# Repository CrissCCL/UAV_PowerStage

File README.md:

# ⚡🔌🔋 UAV Power Distribution & Regulation Board

## Overview

This repository documents an **updated power stage for an unmanned aerial vehicle (UAV)**, developed as a **standalone PCB** to improve system modularity, robustness, and power integrity.

Originally, the power management circuitry was integrated on the same PCB as the **MCU, IMU, and control electronics**.  
In this revision, the power stage was **fully separated into a dedicated board**, enabling a clear functional separation between:

- **Power distribution and regulation**
- **Control, sensing, and navigation electronics**

This modular architecture simplifies debugging, testing, maintenance, and future system upgrades, while improving isolation between high-current and low-power domains.

## 📂 Contents
- `/Hardware` →  Schematic, Gerbers.

## 🌐 YouTube

📺 [Upgrade Power Stage](https://youtube.com/shorts/vSKApaUKDLE?feature=share)

## 🔗 Project Context

This power distribution and regulation board is part of the ongoing hardware updates for the **DIY UAV project**.

The main project repository documents the overall UAV system, including mechanical design, control architecture, and system integration:

- **DIY UAV – Main Project Repository**  
  [DIY UAV](https://github.com/CrissCCL/DIY_UAV)

This repository focuses exclusively on the **power stage modularization**, extracted from the original integrated PCB to improve system scalability, maintainability, and electrical robustness.

## 🧩 System Architecture

The UAV electronics are now divided into two main subsystems:

1. **Power Stage (this repository)**
2. **Control & Sensing Stage (MCU + IMU)**

The power board is responsible for managing the **battery input**, distributing high-current power to the ESCs, and providing regulated power for low-voltage electronics.

## 🔗 Power Flow Architecture

The power distribution follows a centralized architecture in which the battery input is first managed by a high-side power switch, and then distributed to both high-current and low-voltage domains.

## 🖼️ PCB Render Visualization

<table>
  <tr>
    <td align="center">
      <br>
      <sub> Power Stage PCB – Top View </sub>
    </td>
    <td align="center">
        <br>
      <sub>Power Stage PCB – Bottom View </sub>
    </td>
  </tr>
</table>

## ⚡ Physical Prototype

The following image shows the complete setup of the **prototype version**:

<table>
  <tr>
    <td align="center">
      <br>
      <sub> Power Stage PCB V1 – Top View </sub>
    </td>
    <td align="center">
        <br>
      <sub>Power Stage PCB V1 – Bottom View </sub>
    </td>
  </tr>
</table>

## 📸 In-System Integration (UAV Installation)

The following image shows the **power distribution board installed inside the UAV platform**, 
demonstrating real-world integration with the battery, ESCs, and avionics electronics.

<p align="center">
  <sub>Power Stage PCB installed inside the UAV frame – full system integration test</sub>
</p>

## ⚠️ Disclaimer

This project is intended **for educational and experimental purposes only**.

The power distribution and regulation board is **not flight-certified** and has not been validated under aviation or safety-critical standards.

Users are responsible for ensuring safe operation, proper electrical protection, and compliance with applicable regulations when working with high-current systems.

## 🤝 Support projects
 Support me on Patreon [https://www.patreon.com/c/CrissCCL](https://www.patreon.com/c/CrissCCL)

## 📜 License
MIT License

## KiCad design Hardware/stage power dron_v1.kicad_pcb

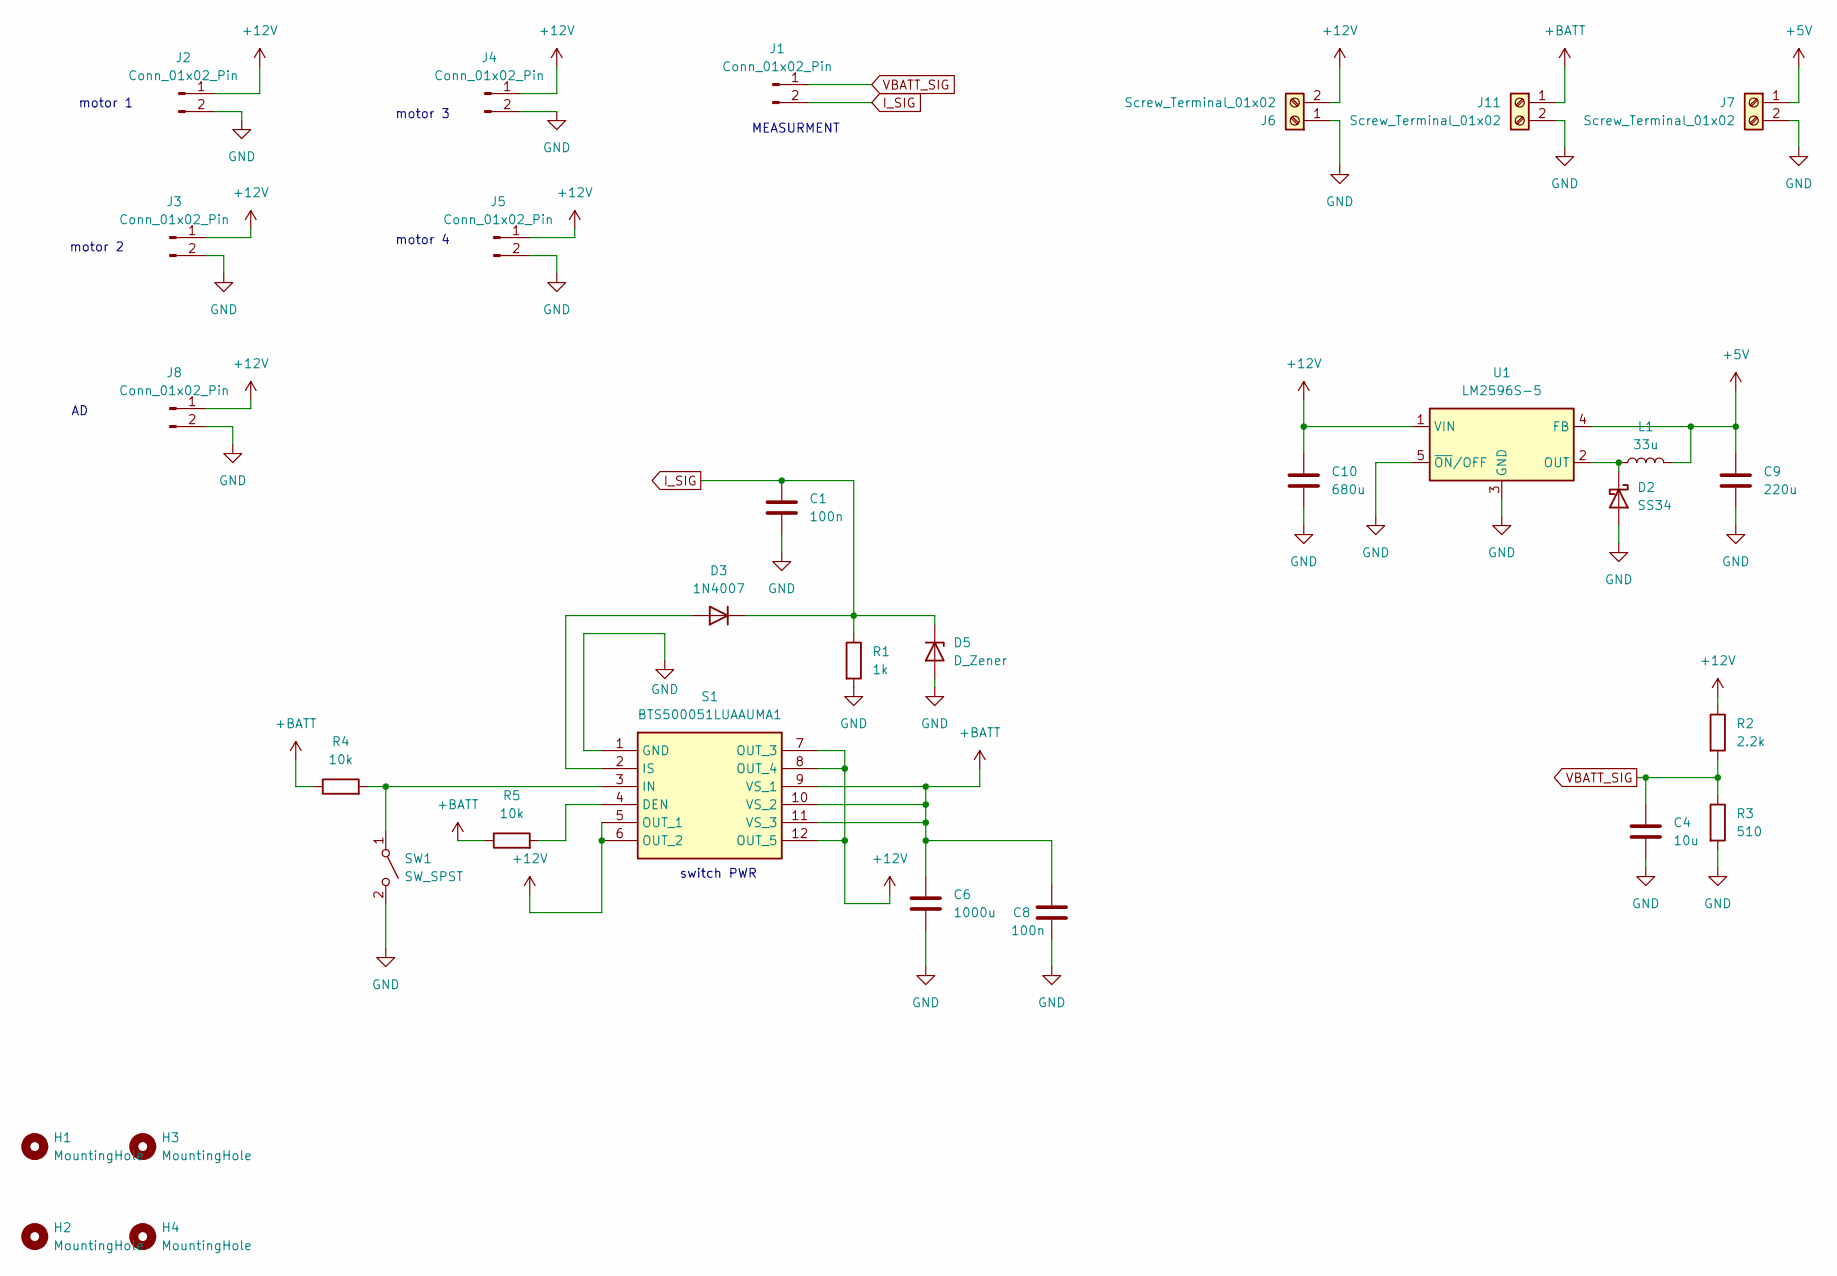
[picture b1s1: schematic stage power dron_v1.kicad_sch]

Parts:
C1, C8: 100n; C_1206_3216Metric_Pad1.33x1.80mm_HandSolder
C4: 10u; CP_Elec_4x5.4
C6: 1000u; CP_Elec_10x10.5
C9: 220u; CP_Elec_6.3x5.4
C10: 680u; CP_Elec_10x10.5
D2: SS34; D_SMA
D3: 1N4007; D_SOD-123
D5: D_Zener; D_MiniMELF
H1, H2, H3, H4: MountingHole; MountingHole_3.2mm_M3_ISO7380_Pad
J1: Conn_01x02_Pin; PinHeader_1x02_P2.54mm_Vertical
J2, J3, J4, J5, J8: Conn_01x02_Pin; conector_pad_1
J6, J7, J11: Screw_Terminal_01x02; TerminalBlock_bornier-2_P5.08mm
L1: 33u; L_12x12mm_H8mm
R1: 1k; R_1206_3216Metric_Pad1.30x1.75mm_HandSolder
R2: 2.2k; R_1206_3216Metric_Pad1.30x1.75mm_HandSolder
R3: 510; R_1206_3216Metric_Pad1.30x1.75mm_HandSolder
R4, R5: 10k; R_1206_3216Metric_Pad1.30x1.75mm_HandSolder
S1: BTS500051LUAAUMA1; Manufacturer_Part_Number BTS500051LUAAUMA1; Mouser Part Number 726-BTS500051LUAAUMA
SW1: SW_SPST; spst 1 grande
U1: LM2596S-5; TO-263-5_TabPin3

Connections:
+5V: C9.1, J7.1, L1.2, U1.4 (FB)
+12V: C10.1, J2.1, J3.1, J4.1, J5.1, J6.2, J8.1, R2.1, S1.5 (OUT_1), S1.6 (OUT_2), S1.7 (OUT_3), S1.8 (OUT_4), S1.12 (OUT_5), U1.1 (VIN)
+BATT: C6.1, C8.1, J11.1, R4.1, R5.1, S1.9 (VS_1), S1.10 (VS_2), S1.11 (VS_3)
GND: C1.2, C4.2, C6.2, C8.2, C9.2, C10.2, D2.2 (A), D5.2 (A), J2.2, J3.2, J4.2, J5.2, J6.1, J7.2, J8.2, J11.2, R1.2, R3.2, S1.1 (GND), SW1.2 (B), U1.3 (GND), U1.5 (~ON/OFF)
I_SIG: C1.1, D3.1 (K), D5.1 (K), J1.2, R1.1
unnamed: D2.1 (K), L1.1, U1.2 (OUT)
unnamed: D3.2 (A), S1.2 (IS)
unnamed: R5.2, S1.4 (DEN)
unnamed: R4.2, S1.3 (IN), SW1.1 (A)
VBATT_SIG: C4.1, J1.1, R2.2, R3.1

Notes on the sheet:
motor 4
motor 1
switch PWR
motor 2
motor 3
MEASURMENT

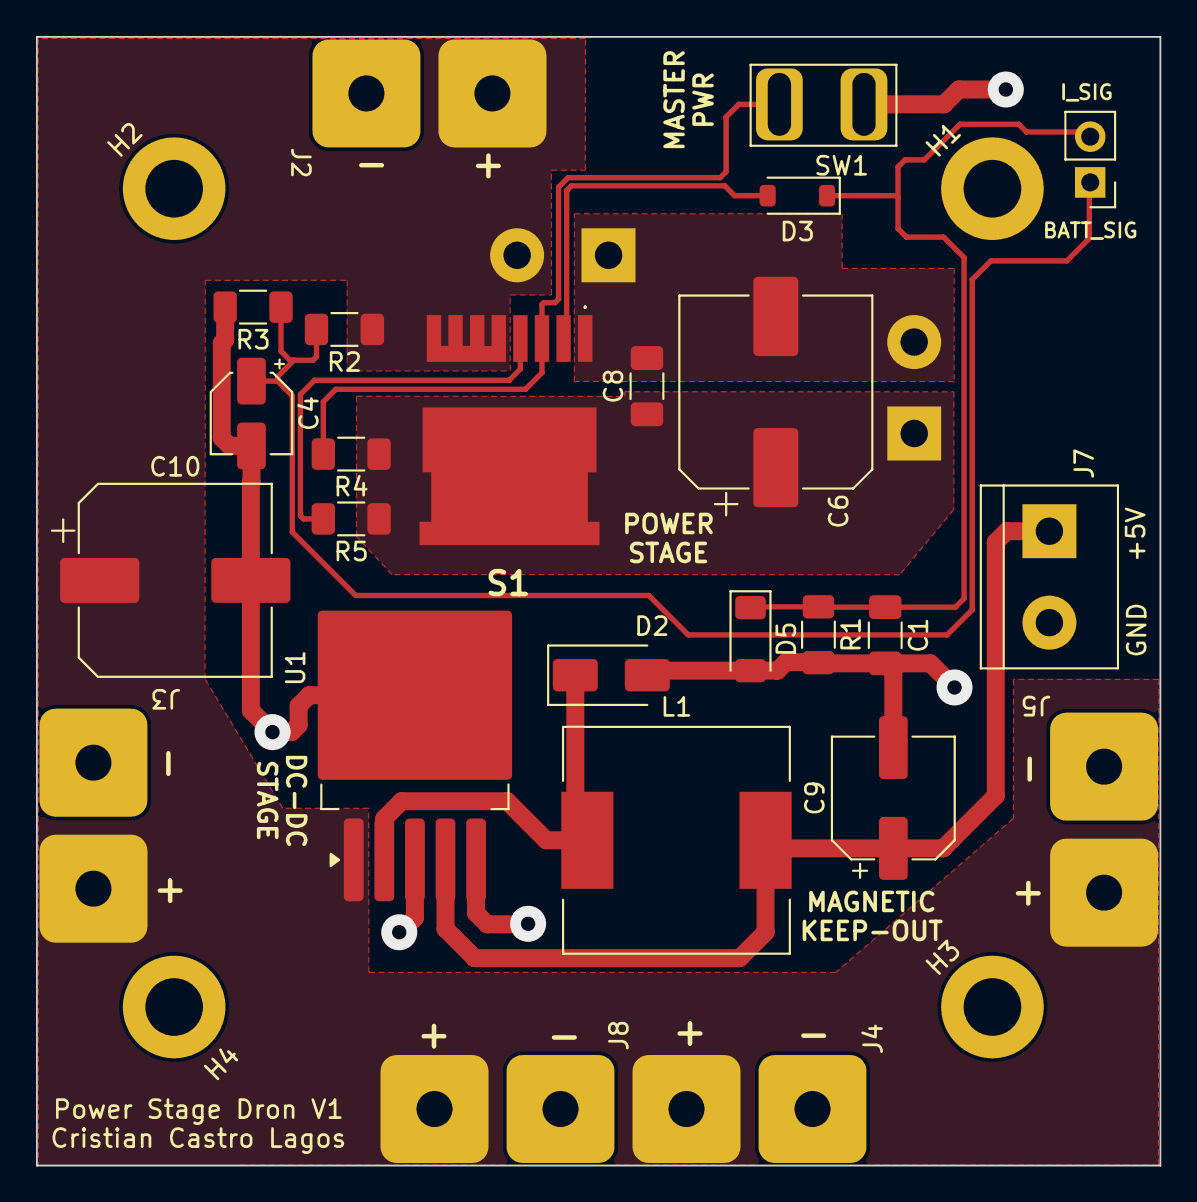
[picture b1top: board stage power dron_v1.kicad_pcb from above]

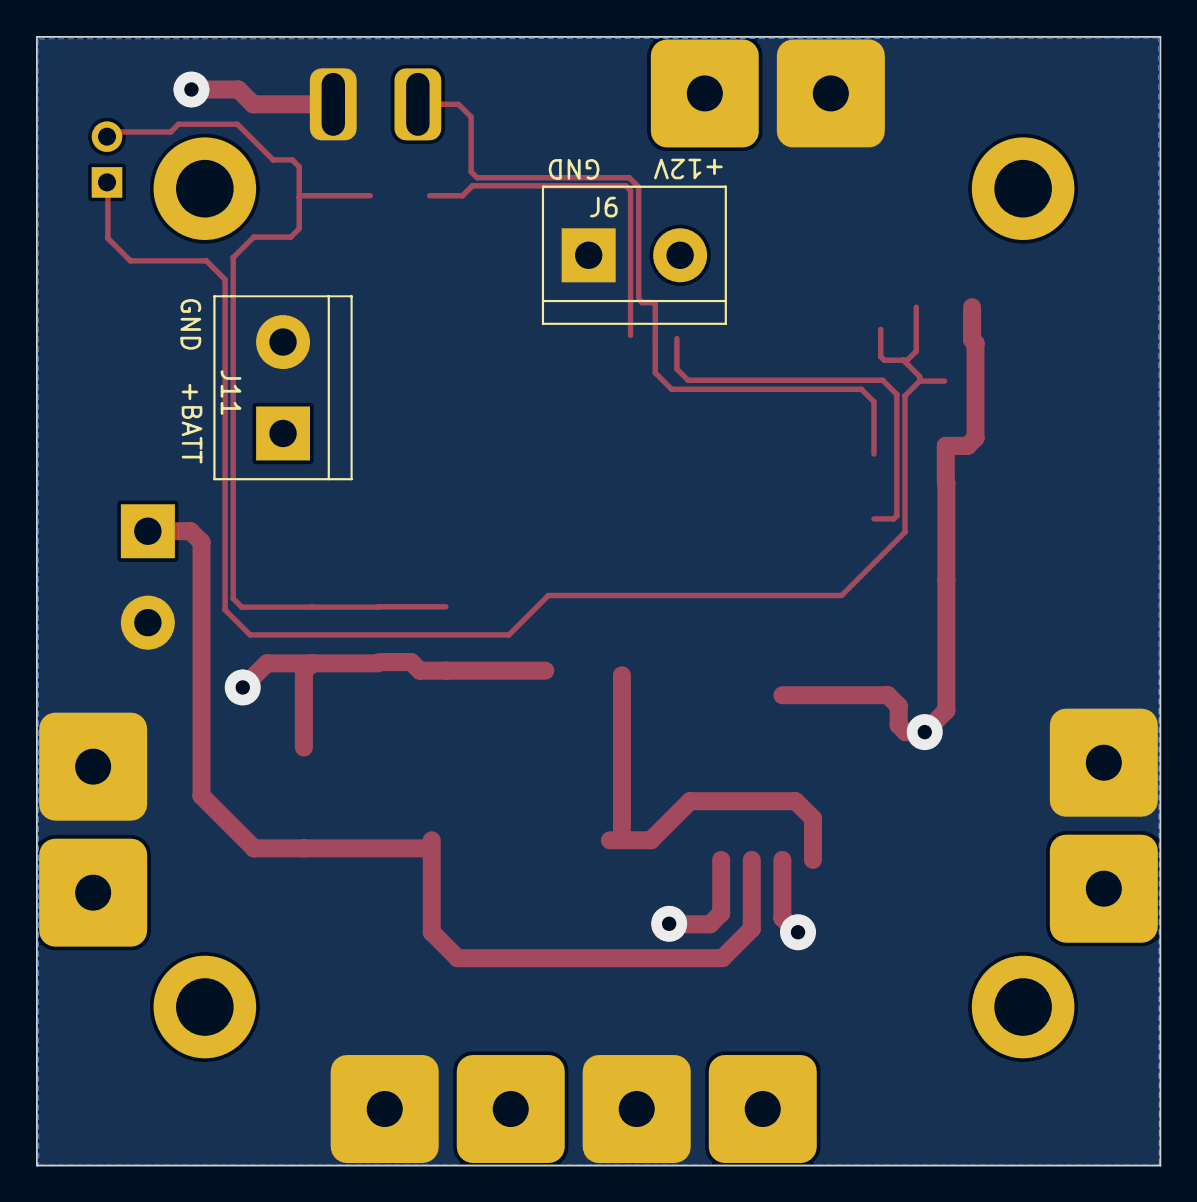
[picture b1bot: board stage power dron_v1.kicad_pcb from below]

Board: 2 copper layers, 62.4 x 62.7 mm, 31 parts (2 on the bottom side), 10 nets.

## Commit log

2025-12-17 Create LICENSE
2025-12-17 Enhance README with power flow and PCB visuals
    Added sections on power flow architecture and PCB visualization.
2025-12-17 Fix formatting issues in README.md
2025-12-17 Add License section to README
2025-12-23 Update Hardware section in README
    Removed PCB from the Hardware section in the README.
2026-01-08 Update image width in README for consistency
2026-01-09 Add YouTube link to README
    Added a YouTube link for the Upgrade Power Stage.
2026-02-07 Update LICENSE
